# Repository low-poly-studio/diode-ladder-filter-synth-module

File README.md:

# diode-ladder-filter-synth-module
 Diode Ladder Filter Synth Module

 Putting this here as I dont have a better place for it at the moment

BL-HUF35A-AV-TRB - Red
TJ-S2012SW8TGLC0A-A5 - orange
BL-HJC36G-AV-TRB - amber
KT-0805Y - yellow, basic
KT-0805YG - yellow green
APT2012CGCK  - green
KT-0805G - emerald
LTST-C170TBKT - blue
E6C0805TKAY1UDA - foggy yellow lense ice blue
GZ2012D101TF - purple
XL-2012UPC - pink
KT-0805W - white

## JLC LED Library
| Colour 	| MF part 		 |  JLC part| Basic? |
|---		    |---			      |---		     |---     |
|red		    |BL-HUF35A-AV-TRB	|		       | |
|orange-red		|ORH-R35A	|	C205444	||
|Orange		|TJ-S2012SW8TGLC0A-A5	|		||
|Amber		|BL-HJC36G-AV-TRB	|	0605!	||
|Yellow		|KT-0805Y		||
|yellow-green	|KT-0805YG	|	|		|
|green		|APT2012CGCK		|	||
|emerald	|KT-0805G		||
|blue		|LTST-C170TBKT	|	|	|
|ice-blue	|E6C0805TKAY1UDA	||		|
|purple		|GZ2012D101TF		|	||
|pink		|XL-2012UPC		|		|	|
|white		|KT-0805W		|	||

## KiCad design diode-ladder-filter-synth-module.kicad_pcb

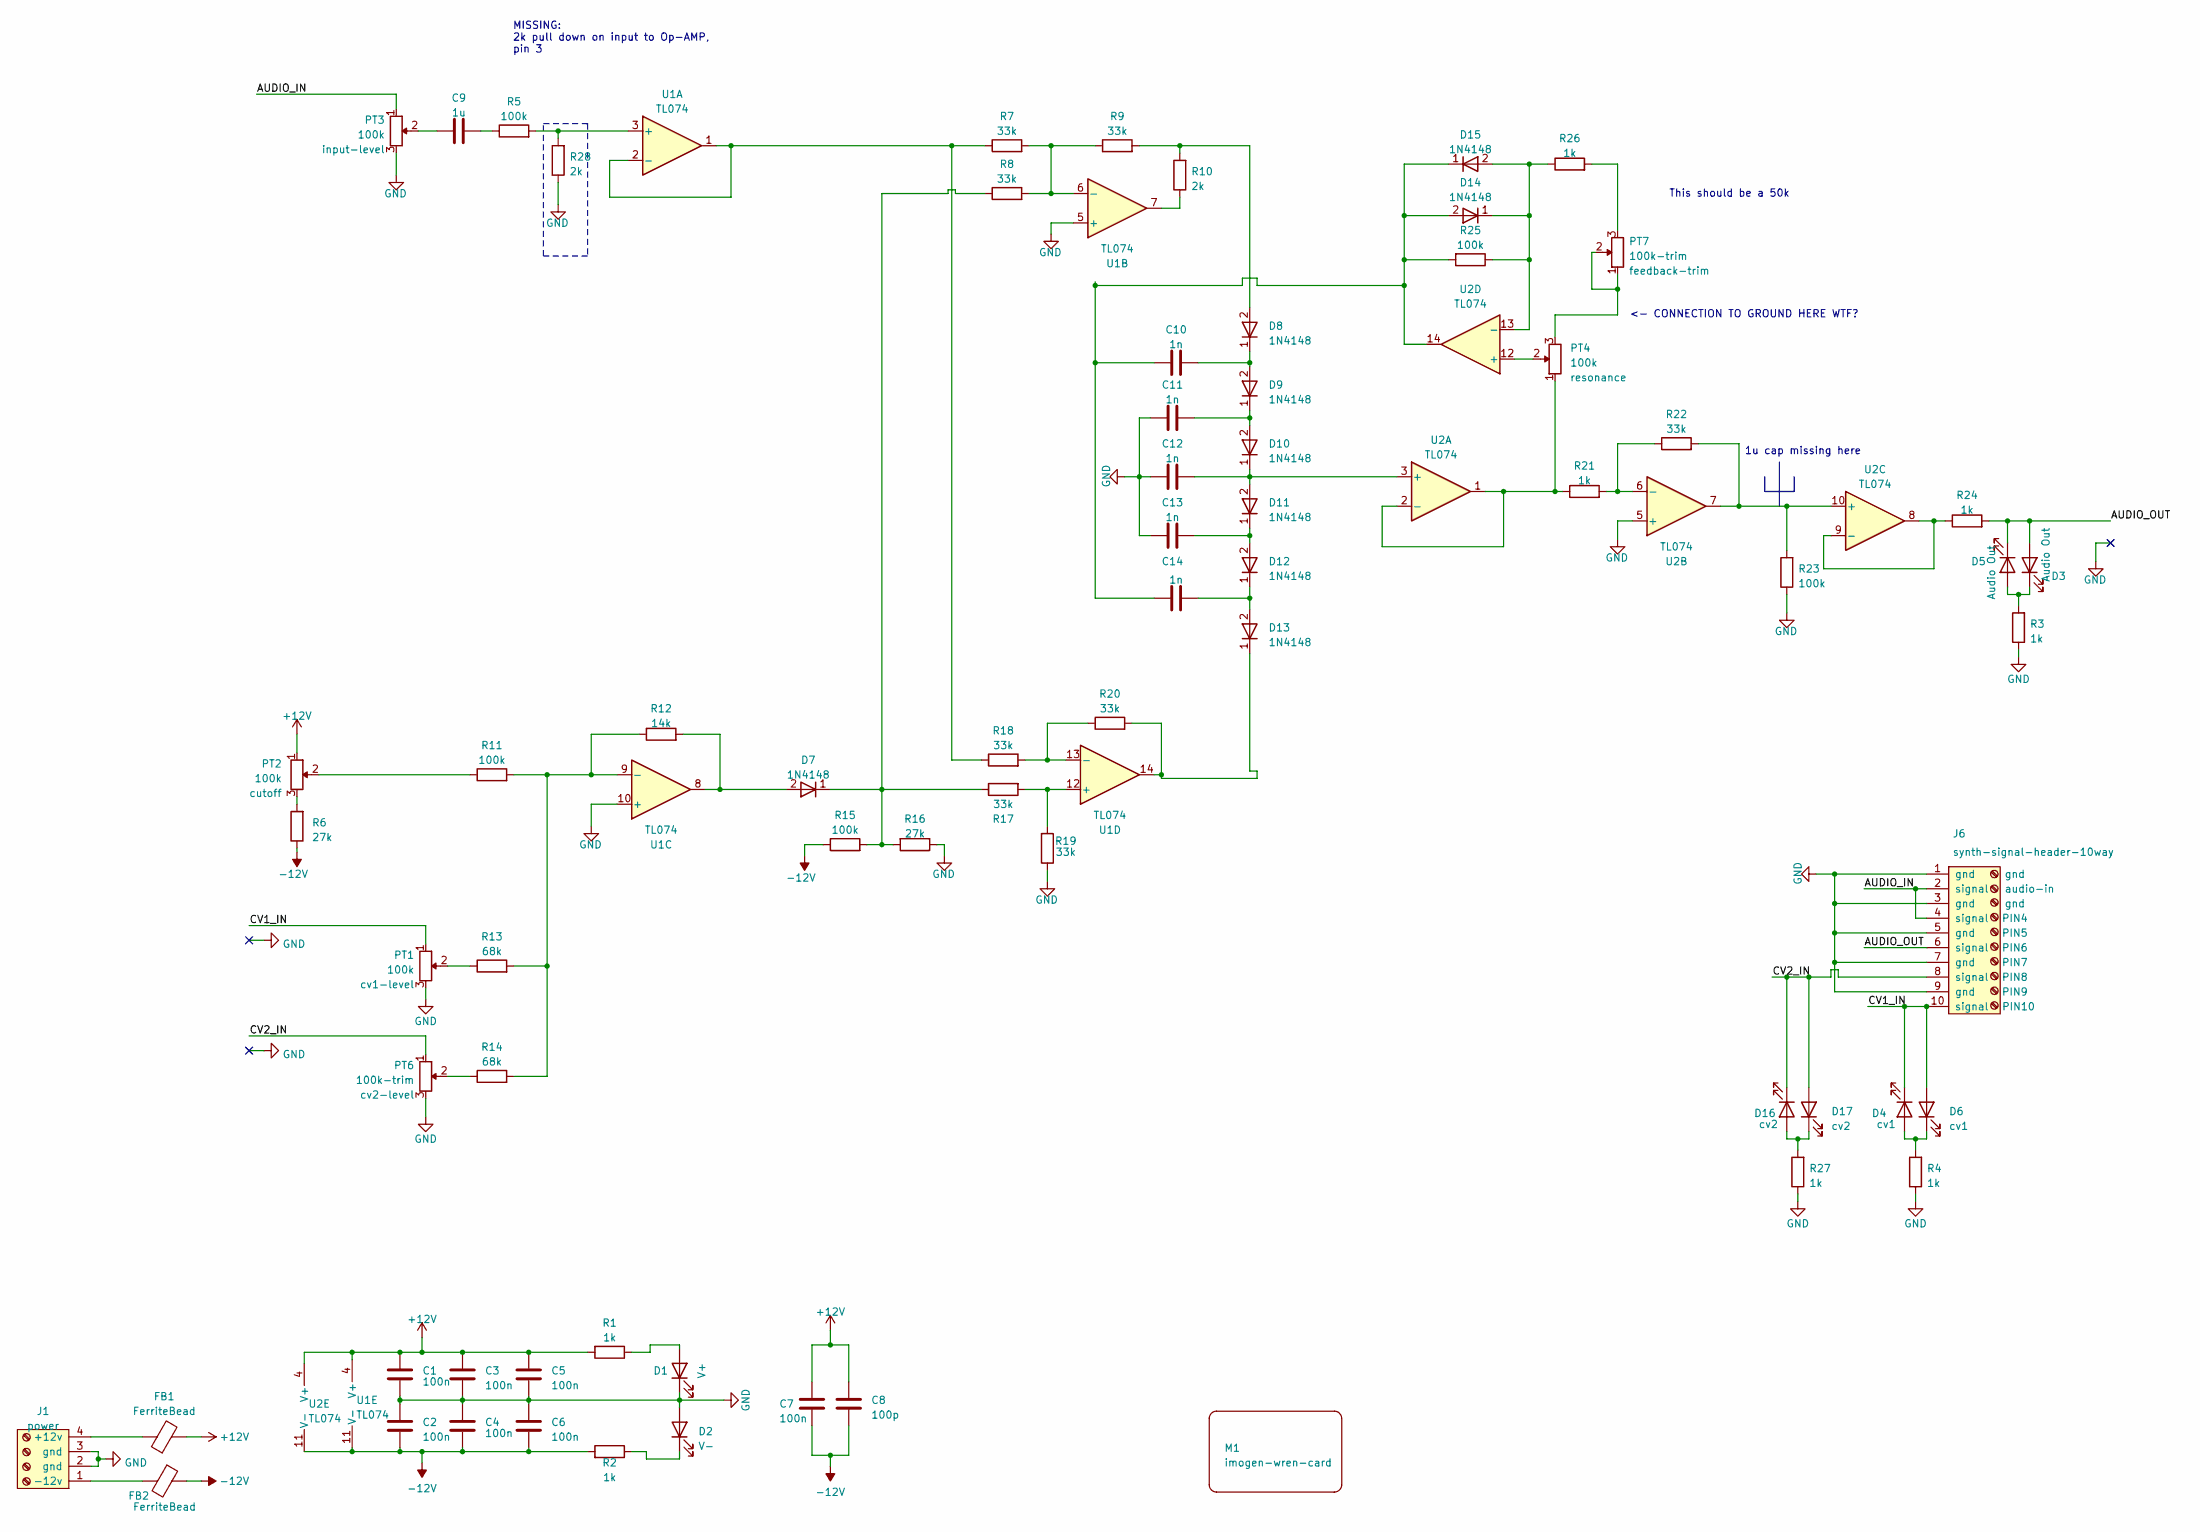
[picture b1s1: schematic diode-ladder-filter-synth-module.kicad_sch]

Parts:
C1, C2, C3, C4, C5, C6, C7: 100n; C_0805_2012_HandSolder_kawaii; JLCpart C779975
C8: 100p; C_0805_2012_HandSolder_kawaii; JLCpart C779975
C9: 1u; C_0805_2012Metric_Pad1.18x1.45mm_HandSolder
C10, C11, C12, C13, C14: 1n; C_0805_2012Metric_Pad1.18x1.45mm_HandSolder
D1: V+; LED_0805_2012_Kawaii; JLCpart C84259
D2: V-; LED_0805_2012_Kawaii; JLCpart C84259
D3, D5: Audio Out; LED_0805_2012_Kawaii; JLCpart C84259
D4, D6: cv1; LED_0805_2012_Kawaii; JLCpart C84259
D7, D8, D9, D10, D11, D12, D13, D14, D15: 1N4148; D_MiniMELF_kawaii
D16, D17: cv2; LED_0805_2012_Kawaii; JLCpart C84259
FB1, FB2: FerriteBead; L_0805_2012Metric_Pad1.05x1.20mm_HandSolder; JLCpart C845115
J1: power; synth-power-termbox-MPT-0,5-4-2.54_1x04_P2.54mm
J6: synth-signal-header-10way; synth-signal-MPT-1x10_P2.54mm_Horizontal_1
M1: imogen-wren-card; credit-card-screws
PT1, PT2, PT3, PT4: 100k; Potentiometer_Alpha-reversable
PT6, PT7: 100k-trim; Potentiometer_Bourns-reversable-1; JLCpart C118911
R1, R2, R3, R4, R21, R24, R26, R27: 1k; R_0805_2012Metric_Pad1.20x1.40mm_HandSolder; JLCpart C218388
R5, R11, R15, R23, R25: 100k; R_0805_2012Metric_Pad1.20x1.40mm_HandSolder; JLCpart C280020
R6, R16: 27k; R_0805_2012Metric_Pad1.20x1.40mm_HandSolder
R7, R8, R9, R17, R18, R19, R20, R22: 33k; R_0805_2012Metric_Pad1.20x1.40mm_HandSolder
R10, R28: 2k; R_0805_2012Metric_Pad1.20x1.40mm_HandSolder
R12: 14k; R_0805_2012Metric_Pad1.20x1.40mm_HandSolder
R13, R14: 68k; R_0805_2012Metric_Pad1.20x1.40mm_HandSolder
U1, U2: TL074; SOIC-14_3.9x8.7mm_P1.27mm

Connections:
+12V: C1.1, C3.1, C5.1, C7.1, C8.2, FB1.2, PT2.1, R1.2, U1.4 (V+), U2.4 (V+)
-12V: C2.2, C4.2, C6.2, C7.2, C8.1, FB2.1, R2.2, R6.1, R15.1, U1.11 (V-), U2.11 (V-)
/AUDIO_IN: J6.2 (signal), J6.4 (signal), PT3.1
/AUDIO_OUT: D3.2 (A), D5.1 (K), J6.6 (signal), R24.2
/CV1_IN: D4.1 (K), D6.2 (A), J6.10 (signal), PT1.1
/CV2_IN: D16.1 (K), D17.2 (A), J6.8 (signal), PT6.1
GND: C1.2, C2.1, C3.2, C4.1, C5.2, C6.1, C11.1, C12.1, C13.1, D1.1 (K), D2.2 (A), J1.2 (gnd), J1.3 (gnd), J6.1 (gnd), J6.3 (gnd), J6.5 (gnd), J6.7 (gnd), J6.9 (gnd), PT1.3, PT3.3, PT6.3, R3.1, R4.1, R16.1, R19.1, R23.1, R27.1, U1.5 (+), U1.10 (+), U2.5 (+)
unnamed: C9.1, PT3.2
unnamed: C9.2, R5.1
unnamed: D1.2 (A), R1.1
unnamed: D2.1 (K), R2.1
unnamed: D3.1 (K), D5.2 (A), R3.2
unnamed: D4.2 (A), D6.1 (K), R4.2
unnamed: D7.2 (A), R12.2, U1.8
unnamed: D7.1 (K), R8.1, R15.2, R16.2, R17.1
unnamed: D8.2 (A), R9.2, R10.2
unnamed: C10.2, D8.1 (K), D9.2 (A)
unnamed: C11.2, D9.1 (K), D10.2 (A)
unnamed: C12.2, D10.1 (K), D11.2 (A), U2.3 (+)
unnamed: C13.2, D11.1 (K), D12.2 (A)
unnamed: C14.2, D12.1 (K), D13.2 (A)
unnamed: D13.1 (K), R20.2, U1.14
unnamed: C10.1, C14.1, D14.2 (A), D15.1 (K), R25.2, U2.14
unnamed: D14.1 (K), D15.2 (A), R25.1, R26.1, U2.13 (-)
unnamed: D16.2 (A), D17.1 (K), R27.2
unnamed: FB1.1, J1.4 (+12v)
unnamed: FB2.2, J1.1 (-12v)
unnamed: PT1.2, R13.1
unnamed: PT2.2, R11.1
unnamed: PT2.3, R6.2
unnamed: PT4.3, PT7.1, PT7.2
unnamed: PT6.2, R14.1
unnamed: PT7.3, R26.2
unnamed: R10.1, U1.7
unnamed: R5.2, U1.3 (+)
unnamed: R7.1, R18.1, U1.1, U1.2 (-)
unnamed: R7.2, R8.2, R9.1, U1.6 (-)
unnamed: R11.2, R12.1, R13.2, R14.2, U1.9 (-)
unnamed: R17.2, R19.2, U1.12 (+)
unnamed: R18.2, R20.1, U1.13 (-)
unnamed: PT4.1, R21.1, U2.1, U2.2 (-)
unnamed: R21.2, R22.1, U2.6 (-)
unnamed: R22.2, R23.2, U2.7, U2.10 (+)
unnamed: R24.1, U2.8, U2.9 (-)
unnamed: PT4.2, U2.12 (+)

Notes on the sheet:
This should be a 50k
<- CONNECTION TO GROUND HERE WTF?
1u cap missing here
MISSING: 2k pull down on input to Op-AMP, pin 3

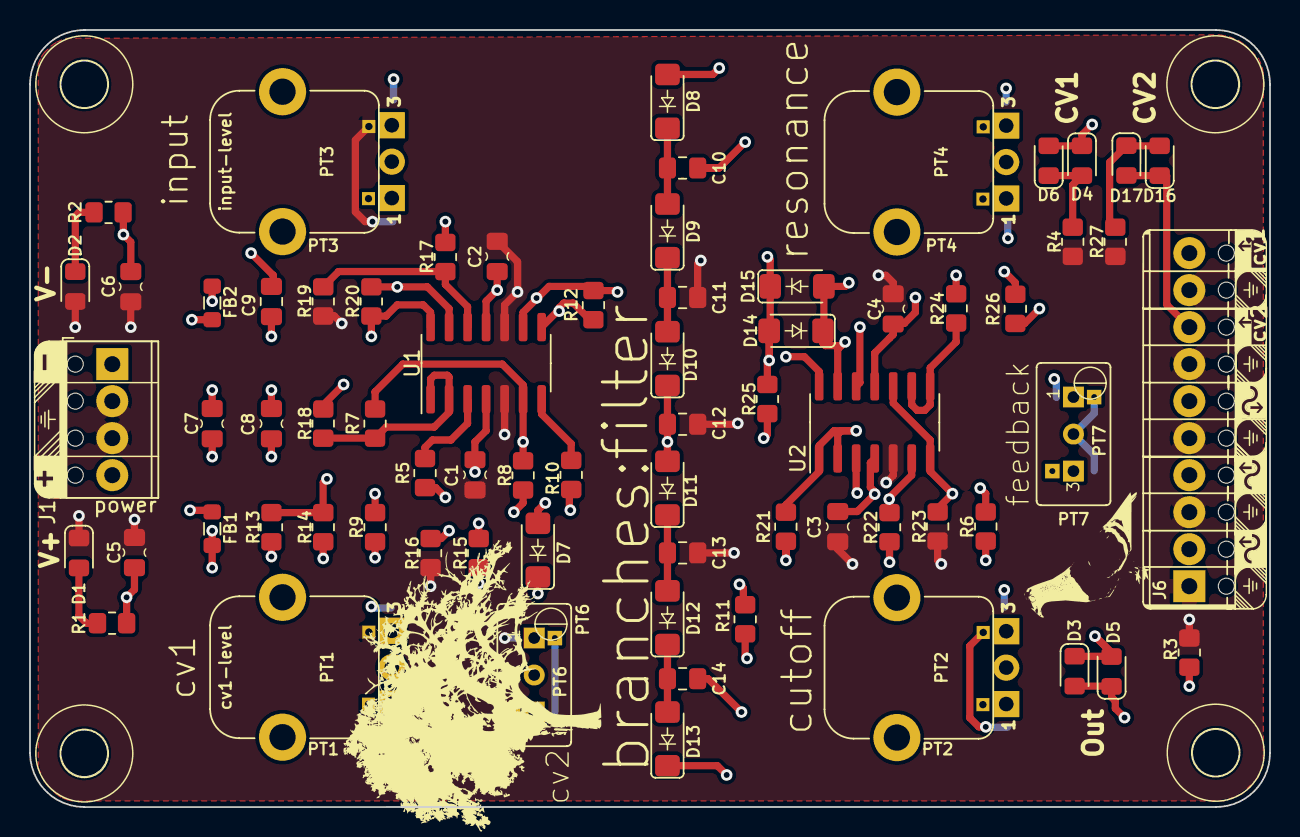
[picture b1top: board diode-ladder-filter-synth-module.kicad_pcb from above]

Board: 4 copper layers, 85.1 x 53.3 mm, 71 parts (0 on the bottom side), 45 nets.

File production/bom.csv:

Designator,Footprint,Quantity,Value,LCSC Part #
"C1, C2, C3, C4, C5, C6, C7",C_0805_2012_HandSolder_kawaii,7,100n,
"C10, C11, C12, C13, C14",0805,5,1n,
C8,C_0805_2012_HandSolder_kawaii,1,100p,
C9,0805,1,1u,
D1,LED_0805_2012_Kawaii,1,V+,
"D10, D11, D12, D13, D14, D15, D7, D8, D9",D_MiniMELF_kawaii,9,1N4148,
"D16, D17",LED_0805_2012_Kawaii,2,cv2,
D2,LED_0805_2012_Kawaii,1,V-,
"D3, D5",LED_0805_2012_Kawaii,2,Audio Out,
"D4, D6",LED_0805_2012_Kawaii,2,cv1,
"FB1, FB2",0805,2,FerriteBead,
J1,"synth-power-termbox-MPT-0,5-4-2.54_1x04_P2.54mm",1,power,
J6,synth-signal-MPT-1x10_P2.54mm_Horizontal_1,1,synth-signal-header-10way,
M1,credit-card-screws,1,imogen-wren-card,
"PT1, PT2, PT3, PT4",Potentiometer_Alpha-reversable,4,100k,
"PT6, PT7",Potentiometer_Bourns-reversable-1,2,100k-trim,
"R1, R2, R21, R24, R26, R27, R3, R4",0805,8,1k,
R10,0805,1,2k,
"R11, R15, R23, R25, R5",0805,5,100k,
R12,0805,1,14k,
"R13, R14",0805,2,68k,
"R16, R6",0805,2,27k,
"R17, R18, R19, R20, R22, R7, R8, R9",0805,8,33k,
"U1, U2",SOIC-14_3.9x8.7mm_P1.27mm,2,TL074,

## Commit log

2025-03-26 finished design & added fabrication outputs
2025-03-27 added JLC LED part nos.
2025-04-08 added steps n stuff
2025-04-10 zdfwe
2025-04-11 found errors against schematic. Retry tonight
2025-04-12 srgwsreg
